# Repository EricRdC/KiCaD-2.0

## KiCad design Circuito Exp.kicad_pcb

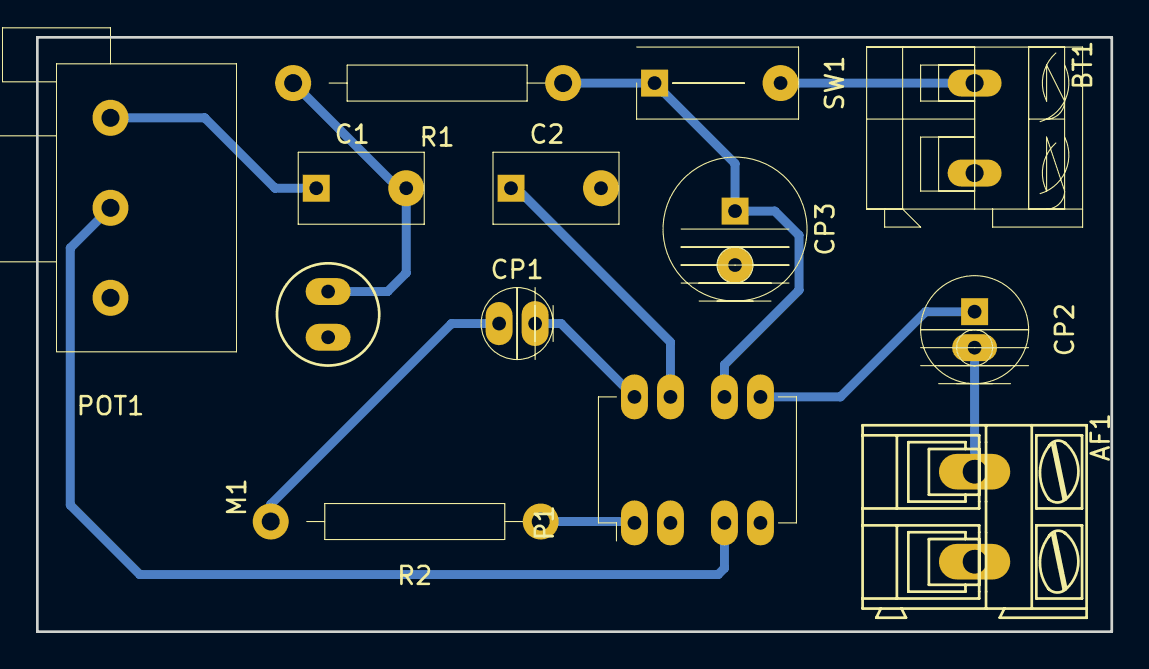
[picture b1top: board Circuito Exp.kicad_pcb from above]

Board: 2 copper layers, 59.7 x 33.0 mm, 13 parts (0 on the bottom side), 12 nets.

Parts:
AF1: Alto-Falante; AK300-2
BT1: 6V; AK300-2
C1, C2: 100nF; C_Disc_D7.5_P5
CP1: 10uF; C_Radial_D5_L11_P2
CP2: 220uF; C_Radial_D7.5_L11.2_P2.5
CP3: 470uF; C_Radial_D8_L11.5_P3.5
M1: Microfone
P1: DIL8; DIP-8_W7.62mm_LongPads
POT1: 10k; Potentiometer_Alps-RK163-single_15mm
R1: 10k; Resistor_Horizontal_RM15mm
R2: 1k2; Resistor_Horizontal_RM15mm
SW1: SPST; SW_DIP_x1_Slide

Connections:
/Negativo: AF1.2, BT1.2, C2.2, CP3.2, M1.2, P1.2, P1.4, POT1.3
/VCC: CP3.1, P1.6, R1.1, SW1.1
unnamed: AF1.1, CP2.2
unnamed: BT1.1, SW1.2
unnamed: C1.1, POT1.1
unnamed: C1.2, M1.1, R1.2
unnamed: C2.1, P1.7
unnamed: CP1.1, R2.2
unnamed: CP1.2, P1.8
unnamed: CP2.1, P1.5
unnamed: P1.1, R2.1
unnamed: P1.3, POT1.2

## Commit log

2018-11-27 100%
